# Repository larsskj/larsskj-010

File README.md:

DCC Sniffer Shield for Arduino Uno 
==================================

### larsskj-010

This is an Arduino Uno shield that can be used as a model railroad DCC packet sniffer. The board holds four pluggable terminal blocks to distribute track power, and an optocoupler that enables the Arduino to monitor DCC traffic.

A couple of pins can be added to easily connect oscilloscopes, protocol analyzers, etc.

The circuitry is based on an article by Neil McKechnie found on [Neil's Blog](https://wakwak2popo.wordpress.com/2020/12/11/dcc-sniffer/).

Using this shield you can get a nice packet sniffer dumping DCC packets to the Arduino USB port using the code found in the [DCCInspector-EX](https://github.com/DCC-EX/DCCInspector-EX) Github repository.

For more information, visit the [project homepage](https://larsskj.org/projects/larsskj-010).

The files provided are project files for [KiCad 5](http://kicad-pcb.org/).

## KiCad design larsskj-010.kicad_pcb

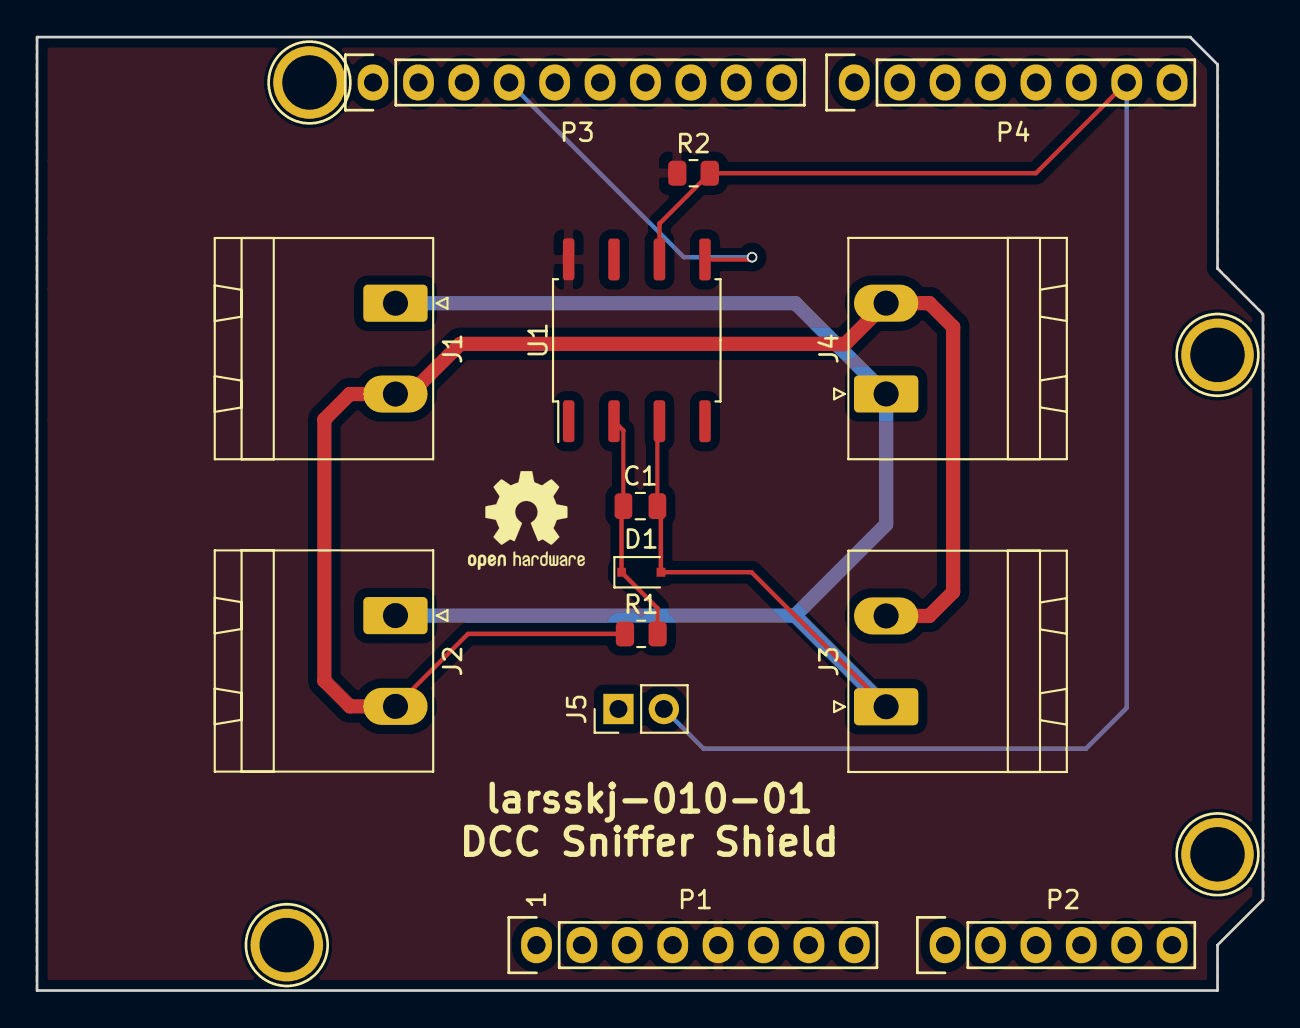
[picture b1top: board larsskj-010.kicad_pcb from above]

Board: 2 copper layers, 68.6 x 53.3 mm, 18 parts (0 on the bottom side), 8 nets.

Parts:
C1: 1nF; C_0805_2012Metric
D1: 1N4148; D_SOD-323F
J1, J2, J3, J4: Conn_01x02; PhoenixContact_MSTBA_2,5_2-G-5,08_1x02_P5.08mm_Horizontal
J5: Conn_01x02_Male; PinHeader_1x02_P2.54mm_Vertical
P1: Power; Socket_Strip_Arduino_1x08
P2: Analog; Socket_Strip_Arduino_1x06
P3: Digital; Socket_Strip_Arduino_1x10
P4: Digital; Socket_Strip_Arduino_1x08
P5, P6, P7, P8: CONN_01X01; Arduino_1pin
R1: 1K; R_0805_2012Metric
R2: 470; R_0805_2012Metric
U1: 6N137; SOP-8_6.62x9.15mm_P2.54mm

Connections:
+5V: P1.5, R2.1, U1.8
/1(Tx): J5.2, P4.7, R2.2, U1.6
/A4(SDA): P2.5, P3.2
/A5(SCL): P2.6, P3.1
GND: J5.1, P1.6, P1.7, P3.4, U1.5
unnamed: C1.1, D1.1, R1.2, U1.2
unnamed: C1.2, D1.2, J1.1, J2.1, J3.1, J4.1, U1.3
unnamed: J1.2, J2.2, J3.2, J4.2, R1.1

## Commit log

2021-08-26 Files added.
